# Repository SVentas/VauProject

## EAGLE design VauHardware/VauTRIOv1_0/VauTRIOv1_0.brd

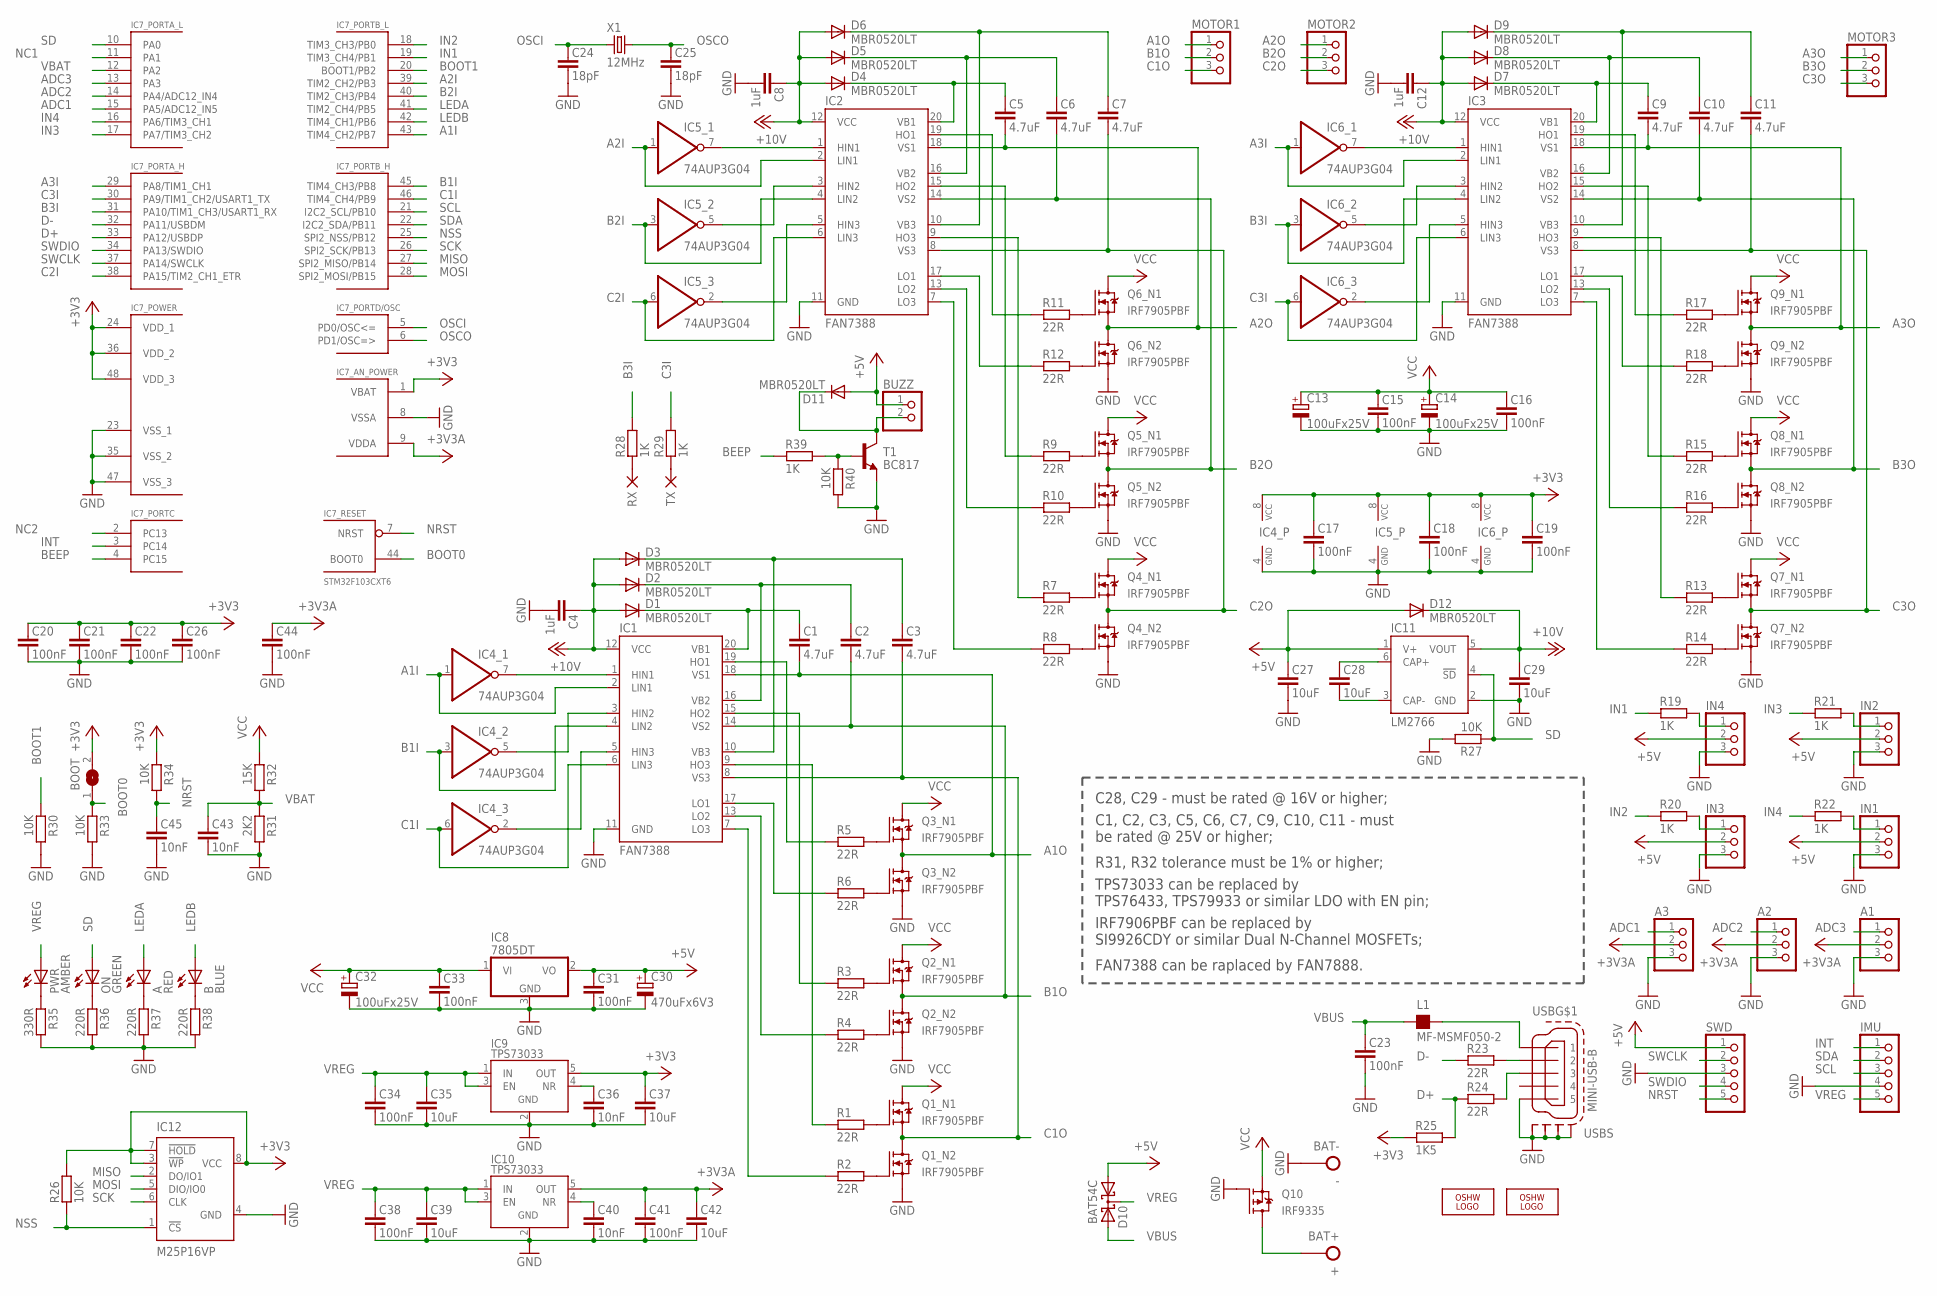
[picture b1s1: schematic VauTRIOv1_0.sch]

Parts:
+: BAT+; PAD20S
-: BAT-; PAD20R
A: RED; CHIPLED_0805
A1, A2, A3: PINHD-1X3; 1X03
B: BLUE; CHIPLED_0805
BOOT: SJ
BUZZ: PINHD-1X2; 1X02
C1, C2, C3, C5, C6, C7, C9, C10, C11: 4.7uF; C0805
C4, C8, C12: 1uF; C0603G
C13, C14: 100uFx25V; E2,5-7
C15, C16, C17, C18, C19, C20, C21, C22, C23, C26, C31, C33, C34, C38, C41, C44: 100nF; C0603G
C24, C25: 18pF; C0603G
C27, C29, C35, C37, C39, C42: 10uF; C0805G
C28: 10uF; C0805
C30: 470uFx6V3; SMC_D
C32: 100uFx25V; SMC_D
C36, C40, C43, C45: 10nF; C0603G
D1, D2, D3, D4, D5, D6, D7, D8, D9, D11, D12: MBR0520LT; SOD123
D10: BAT54C; SOT23
IC1, IC2, IC3: FAN7388; SOIC-20
IC4, IC5, IC6: 74AUP3G04; R-PDSO-G8
IC7: STM32F103CXT6; LQFP48
IC8: 7805DT; TO252
IC9, IC10: TPS73033; SOT23-5
IC11: LM2766; SOT23-6
IC12: M25P16VP; SOIC-8
IMU: PINHD-1X5; 1X05
IN1, IN2, IN3, IN4: PINHD-1X3; 1X03
L1: MF-MSMF050-2; L0603
LOGO1: OSHW_LOGO_10MILX0350-NT; OSHW_10X350_NOTEXT
LOGO2: OSHW_LOGO_FILLX0150-NT; OSHW_FILLX150_NOTEXT
MOTOR1, MOTOR2, MOTOR3: PINHD-1X3MOT; 1X03M
ON: GREEN; CHIPLED_0805
PWR: AMBER; CHIPLED_0805
Q1, Q2, Q3, Q4, Q5, Q6, Q7, Q8, Q9: IRF7905PBF; SOIC-8
Q10: IRF9335; SOIC-8
R1, R2, R3, R4, R5, R6, R7, R8, R9, R10, R11, R12, R13, R14, R15, R16, R17, R18, R23, R24: 22R; R0603
R19, R20, R21, R22, R28, R29, R39: 1K; R0603
R25: 1K5; R0603
R26, R34: 10K; R0603
R27, R30, R33, R40: 10K; R0603G
R31: 2K2; R0603G
R32: 15K; R0603
R35: 330R; R0603G
R36, R37, R38: 220R; R0603G
RX: PAD-SMD10R; SMD10R
SWD: PINHD-1X5; 1X05
T1: BC817; SOT23-BEC
TX: PAD-SMD10R; SMD10R
USB: MINI-USB-B; 32005-201
X1: 12MHz; HC49/S

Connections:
+3V3: BOOT.2, C17.1, C18.1, C19.1, C20.1, C21.1, C22.1, C26.1, C37.1, IC4.8 (VCC), IC5.8 (VCC), IC6.8 (VCC), IC7.1 (VBAT), IC7.24 (VDD_1), IC7.36 (VDD_2), IC7.48 (VDD_3), IC9.5 (OUT), IC12.3 (!WP), IC12.7 (!HOLD), IC12.8 (VCC), R25.1, R26.2, R34.1
+3V3A: A1.2, A2.2, A3.2, C41.1, C42.1, C44.1, IC7.9 (VDDA), IC10.5 (OUT)
+5V: BUZZ.1, C27.1, C30.+, C31.1, D10.1 (A1), D11.A, D12.A, IC8.2 (VO), IC11.1 (V+), IN1.2, IN2.2, IN3.2, IN4.2, SWD.1
+12V: C4.1, C8.1, C12.1, C29.1, D1.A, D2.A, D3.A, D4.A, D5.A, D6.A, D7.A, D8.A, D9.A, D12.C, IC1.12 (VCC), IC2.12 (VCC), IC3.12 (VCC), IC11.5 (VOUT)
A1I: IC1.2 (LIN1), IC4.1 (A), IC7.43 (TIM4_CH2/PB7)
A1O: C1.2, IC1.18 (VS1), MOTOR1.1, Q3.3 (N-S), Q3.7 (N-D), Q3.8 (N-D)
A2I: IC2.2 (LIN1), IC5.1 (A), IC7.39 (TIM2_CH2/PB3)
A2O: C5.2, IC2.18 (VS1), MOTOR2.1, Q6.3 (N-S), Q6.7 (N-D), Q6.8 (N-D)
A3I: IC3.2 (LIN1), IC6.1 (A), IC7.29 (PA8/TIM1_CH1)
A3O: C9.2, IC3.18 (VS1), MOTOR3.1, Q9.3 (N-S), Q9.7 (N-D), Q9.8 (N-D)
ADC1: A3.1, IC7.15 (PA5/ADC12_IN5)
ADC2: A2.1, IC7.14 (PA4/ADC12_IN4)
ADC3: A1.1, IC7.13 (PA3)
B1I: IC1.4 (LIN2), IC4.3 (A), IC7.45 (TIM4_CH3/PB8)
B1O: C2.2, IC1.14 (VS2), MOTOR1.2, Q2.3 (N-S), Q2.7 (N-D), Q2.8 (N-D)
B2I: IC2.4 (LIN2), IC5.3 (A), IC7.40 (TIM2_CH3/PB4)
B2O: C6.2, IC2.14 (VS2), MOTOR2.2, Q5.3 (N-S), Q5.7 (N-D), Q5.8 (N-D)
B3I: IC3.4 (LIN2), IC6.3 (A), IC7.31 (PA10/TIM1_CH3/USART1_RX), R28.2
B3O: C10.2, IC3.14 (VS2), MOTOR3.2, Q8.3 (N-S), Q8.7 (N-D), Q8.8 (N-D)
BAT+: +.P$1, Q10.5 (P-D), Q10.6 (P-D), Q10.7 (P-D), Q10.8 (P-D)
BEEP: IC7.4 (PC15), R39.1
BOOT0: BOOT.1, IC7.44 (BOOT0), R33.1
BOOT1: IC7.20 (BOOT1/PB2), R30.1
C1I: IC1.6 (LIN3), IC4.6 (A), IC7.46 (TIM4_CH4/PB9)
C1O: C3.2, IC1.8 (VS3), MOTOR1.3, Q1.3 (N-S), Q1.7 (N-D), Q1.8 (N-D)
C2I: IC2.6 (LIN3), IC5.6 (A), IC7.38 (PA15/TIM2_CH1_ETR)
C2O: C7.2, IC2.8 (VS3), MOTOR2.3, Q4.3 (N-S), Q4.7 (N-D), Q4.8 (N-D)
C3I: IC3.6 (LIN3), IC6.6 (A), IC7.30 (PA9/TIM1_CH2/USART1_TX), R29.2
C3O: C11.2, IC3.8 (VS3), MOTOR3.3, Q7.3 (N-S), Q7.7 (N-D), Q7.8 (N-D)
D+: IC7.33 (PA12/USBDP), R24.1, R25.2
D-: IC7.32 (PA11/USBDM), R23.1
GND: -.P$1, A1.3, A2.3, A3.3, C4.2, C8.2, C12.2, C13.-, C14.-, C15.2, C16.2, C17.2, C18.2, C19.2, C20.2, C21.2, C22.2, C23.2, C24.2, C25.2, C26.2, C27.2, C29.2, C30.-, C31.2, C32.-, C33.2, C34.2, C35.2, C36.2, C37.2, C38.2, C39.2, C40.2, C41.2, C42.2, C43.2, C44.2, C45.2, IC1.11 (GND), IC2.11 (GND), IC3.11 (GND), IC4.4 (GND), IC5.4 (GND), IC6.4 (GND), IC7.8 (VSSA), IC7.23 (VSS_1), IC7.35 (VSS_2), IC7.47 (VSS_3), IC8.3 (GND), IC9.2 (GND), IC10.2 (GND), IC11.2 (GND), IC12.4 (GND), IMU.4, IN1.3, IN2.3, IN3.3, IN4.3, Q1.1 (N-S), Q2.1 (N-S), Q3.1 (N-S), Q4.1 (N-S), Q5.1 (N-S), Q6.1 (N-S), Q7.1 (N-S), Q8.1 (N-S), Q9.1 (N-S), Q10.4 (P-G), R27.2, R30.2, R31.2, R33.2, R35.2, R36.2, R37.2, R38.2, R40.2, SWD.3, T1.E, USB.5, USB.M1 (S1), USB.M2 (S2), USB.M3 (S3), USB.M4 (S4)
IN1: IC7.19 (TIM3_CH4/PB1), R19.1
IN2: IC7.18 (TIM3_CH3/PB0), R20.1
IN3: IC7.17 (PA7/TIM3_CH2), R21.1
IN4: IC7.16 (PA6/TIM3_CH1), R22.1
INT: IC7.3 (PC14), IMU.1
LEDA: A.A, IC7.41 (TIM2_CH4/PB5)
LEDB: B.A, IC7.42 (TIM4_CH1/PB6)
MISO: IC7.27 (SPI2_MISO/PB14), IC12.2 (DO/IO1)
MOSI: IC7.28 (SPI2_MOSI/PB15), IC12.5 (DIO/IO0)
unnamed: IC1.19 (HO1), R5.1
unnamed: Q5.4 (N-G), R9.2
unnamed: Q5.2 (N-G), R10.2
unnamed: Q2.4 (N-G), R3.2
unnamed: Q2.2 (N-G), R4.2
unnamed: Q3.4 (N-G), R5.2
unnamed: Q3.2 (N-G), R6.2
unnamed: IC1.3 (HIN2), IC4.5 (Y)
unnamed: C1.1, D1.C, IC1.20 (VB1)
unnamed: C2.1, D2.C, IC1.16 (VB2)
unnamed: C3.1, D3.C, IC1.10 (VB3)
unnamed: Q6.4 (N-G), R11.2
unnamed: Q6.2 (N-G), R12.2
unnamed: IN4.1, R19.2
unnamed: Q1.4 (N-G), R1.2
unnamed: Q1.2 (N-G), R2.2
unnamed: IC1.1 (HIN1), IC4.7 (Y)
unnamed: PWR.C, R35.1
unnamed: IC1.5 (HIN3), IC4.2 (Y)
unnamed: ON.C, R36.1
unnamed: R23.2, USB.2
unnamed: A.C, R37.1
unnamed: C5.1, D4.C, IC2.20 (VB1)
unnamed: C6.1, D5.C, IC2.16 (VB2)
unnamed: IC1.17 (LO1), R6.1
unnamed: IC1.15 (HO2), R3.1
unnamed: IC1.13 (LO2), R4.1
unnamed: IC1.7 (LO3), R2.1
unnamed: IC1.9 (HO3), R1.1
unnamed: C7.1, D6.C, IC2.10 (VB3)
unnamed: Q4.4 (N-G), R7.2
unnamed: Q4.2 (N-G), R8.2
unnamed: IC2.1 (HIN1), IC5.7 (Y)
unnamed: IN3.1, R20.2
unnamed: IC2.3 (HIN2), IC5.5 (Y)
unnamed: R24.2, USB.3
unnamed: IC2.5 (HIN3), IC5.2 (Y)
unnamed: IN2.1, R21.2
unnamed: IC2.17 (LO1), R12.1
unnamed: IC2.15 (HO2), R9.1
unnamed: IC2.13 (LO2), R10.1
unnamed: IC2.7 (LO3), R8.1
unnamed: IC2.9 (HO3), R7.1
unnamed: IC2.19 (HO1), R11.1
unnamed: Q8.4 (N-G), R15.2
unnamed: Q8.2 (N-G), R16.2
unnamed: Q9.4 (N-G), R17.2
unnamed: Q9.2 (N-G), R18.2
unnamed: IN1.1, R22.2
unnamed: C9.1, D7.C, IC3.20 (VB1)
unnamed: C10.1, D8.C, IC3.16 (VB2)
unnamed: C11.1, D9.C, IC3.10 (VB3)
unnamed: Q7.4 (N-G), R13.2
unnamed: Q7.2 (N-G), R14.2
unnamed: IC3.1 (HIN1), IC6.7 (Y)
unnamed: L1.2, USB.1
unnamed: IC3.3 (HIN2), IC6.5 (Y)
unnamed: B.C, R38.1
unnamed: IC3.5 (HIN3), IC6.2 (Y)
unnamed: BUZZ.2, D11.C, T1.C
unnamed: IC3.17 (LO1), R18.1
unnamed: IC3.15 (HO2), R15.1
unnamed: IC3.13 (LO2), R16.1
unnamed: IC3.7 (LO3), R14.1
unnamed: IC3.9 (HO3), R13.1
unnamed: IC3.19 (HO1), R17.1
unnamed: C28.1, IC11.6 (CAP+)
unnamed: C28.2, IC11.3 (CAP-)
unnamed: R28.1, RX.PAD
unnamed: R29.1, TX.PAD
unnamed: R39.2, R40.1, T1.B
unnamed: C40.1, IC10.4 (NR)
unnamed: C36.1, IC9.4 (NR)
NC1: IC7.11 (PA1)
NC2: IC7.2 (PC13)
NRST: C45.1, IC7.7 (NRST), R34.2, SWD.5
NSS: IC7.25 (SPI2_NSS/PB12), IC12.1 (!CS), R26.1
OSCI: C24.1, IC7.5 (PD0/OSC<=), X1.1
OSCO: C25.1, IC7.6 (PD1/OSC=>), X1.2
SCK: IC7.26 (SPI2_SCK/PB13), IC12.6 (CLK)
SCL: IC7.21 (I2C2_SCL/PB10), IMU.3
SD: IC7.10 (PA0), IC11.4 (!SD), ON.A, R27.1
SDA: IC7.22 (I2C2_SDA/PB11), IMU.2
SWCLK: IC7.37 (PA14/SWCLK), SWD.2
SWDIO: IC7.34 (PA13/SWDIO), SWD.4
VBAT: C43.1, IC7.12 (PA2), R31.1, R32.2
VBUS: C23.1, D10.2 (A2), L1.1
VCC: C13.+, C14.+, C15.1, C16.1, C32.+, C33.1, IC8.1 (VI), Q1.5 (N-D), Q1.6 (N-D), Q2.5 (N-D), Q2.6 (N-D), Q3.5 (N-D), Q3.6 (N-D), Q4.5 (N-D), Q4.6 (N-D), Q5.5 (N-D), Q5.6 (N-D), Q6.5 (N-D), Q6.6 (N-D), Q7.5 (N-D), Q7.6 (N-D), Q8.5 (N-D), Q8.6 (N-D), Q9.5 (N-D), Q9.6 (N-D), Q10.1 (P-S), Q10.2 (P-S), Q10.3 (P-S), R32.1
VREG: C34.1, C35.1, C38.1, C39.1, D10.3 (CC), IC9.1 (IN), IC9.3 (EN), IC10.1 (IN), IC10.3 (EN), IMU.5, PWR.A

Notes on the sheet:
C1, C2, C3, C5, C6, C7, C9, C10, C11 - must be rated @ 25V or higher;
C28, C29 - must be rated @ 16V or higher;
TPS73033 can be replaced by TPS76433, TPS79933 or similar LDO with EN pin;
IRF7906PBF can be replaced by SI9926CDY or similar Dual N-Channel MOSFETs;
R31, R32 tolerance must be 1% or higher;
FAN7388 can be raplaced by FAN7888.

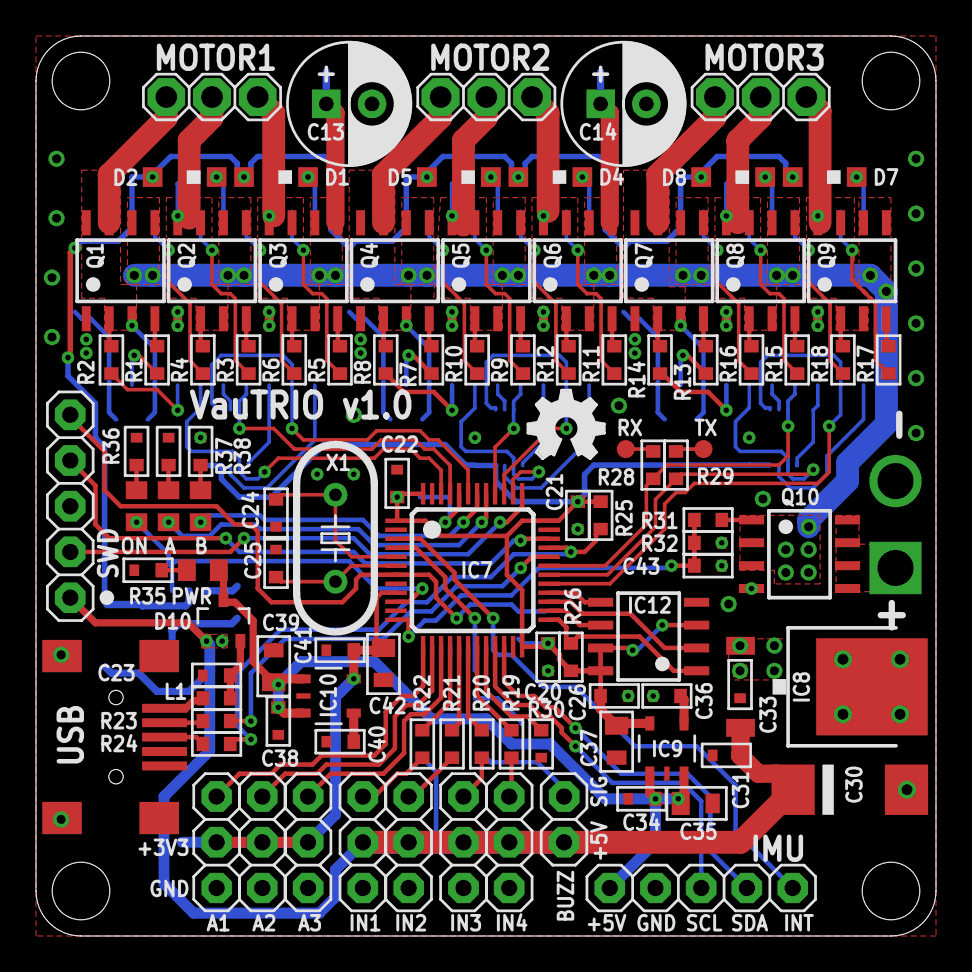
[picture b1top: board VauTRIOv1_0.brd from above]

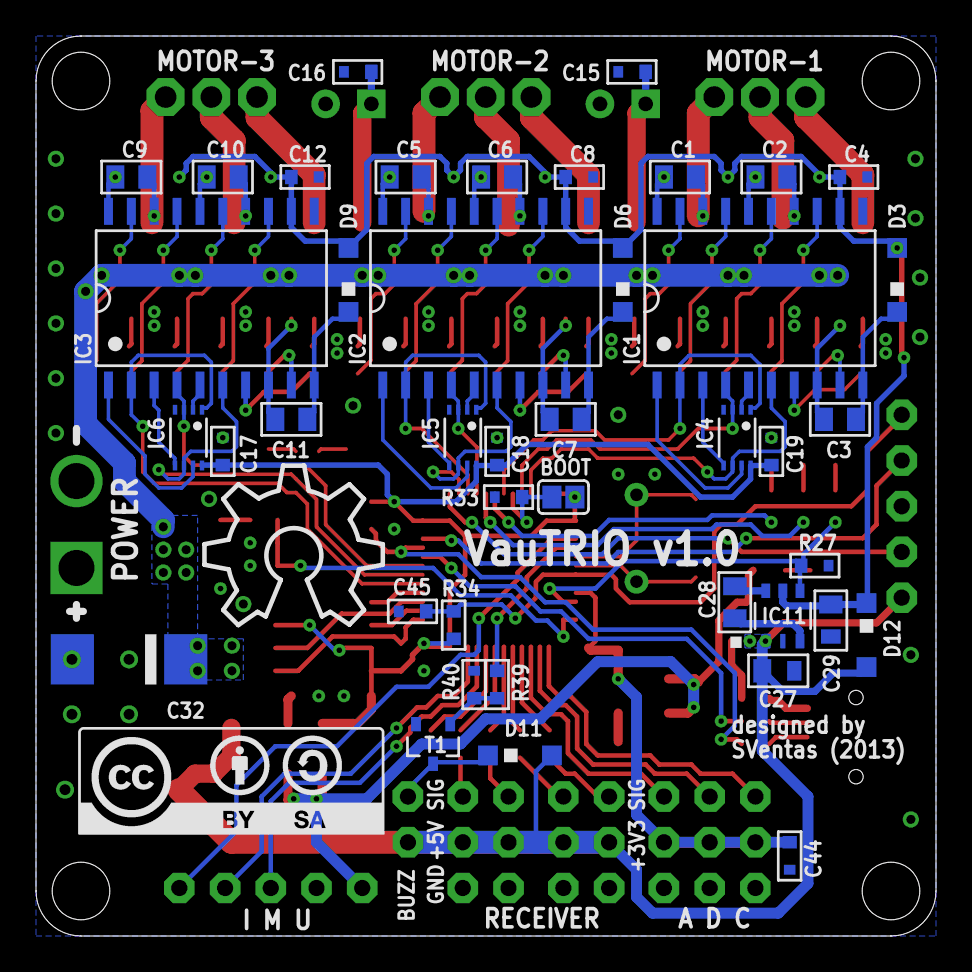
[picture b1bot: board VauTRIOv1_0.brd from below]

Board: 2 copper layers, 50.0 x 50.0 mm, 147 parts (43 on the bottom side), 128 nets.

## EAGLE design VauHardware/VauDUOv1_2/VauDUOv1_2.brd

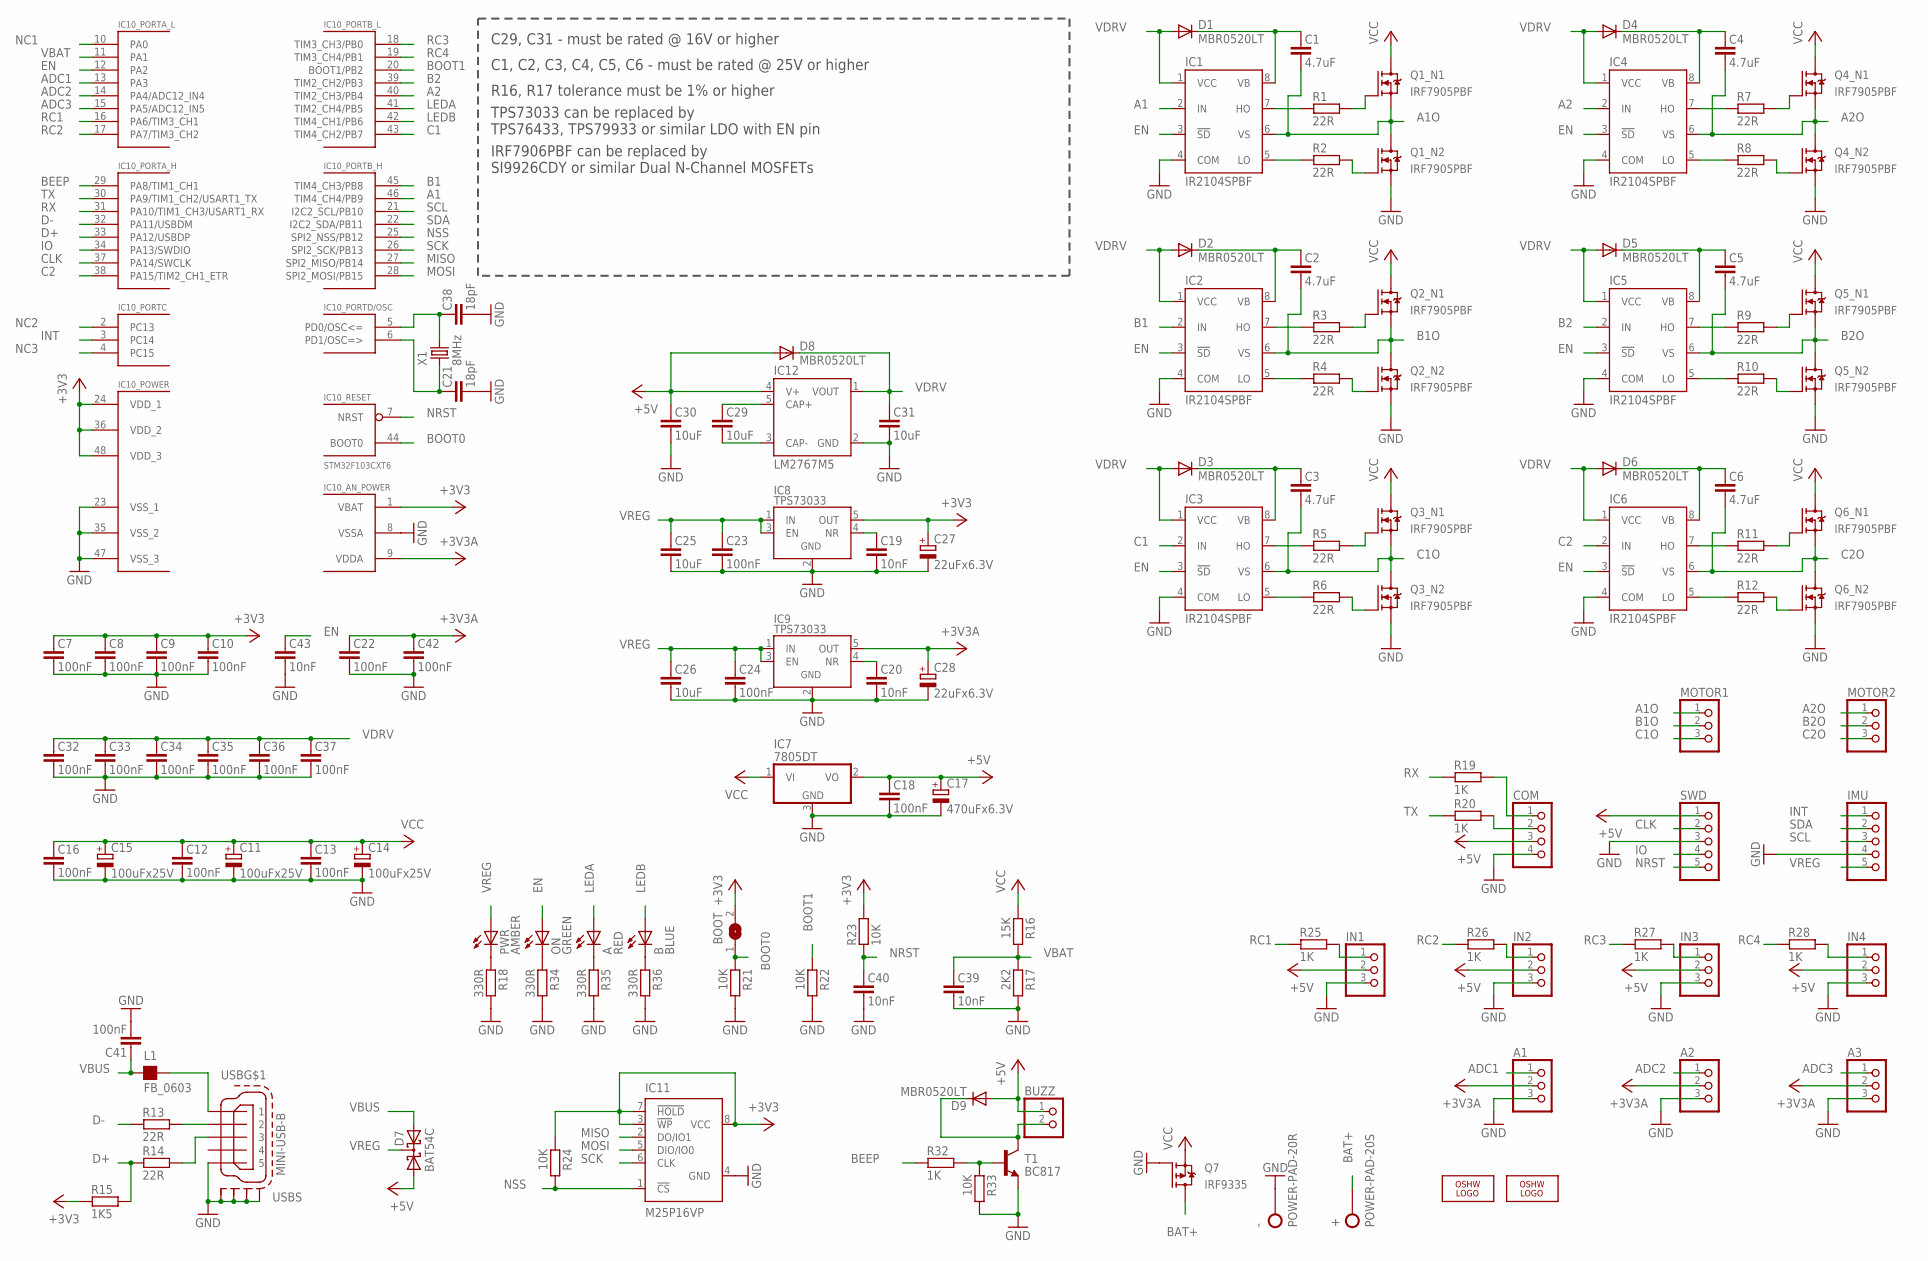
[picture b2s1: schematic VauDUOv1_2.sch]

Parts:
+: POWER-PAD-20S; PAD20S
-: POWER-PAD-20R; PAD20R
A: RED; CHIPLED_0805
A1, A2, A3: PINHD-1X3; 1X03
B: BLUE; CHIPLED_0805
BOOT: SJ
BUZZ: PINHD-1X2; 1X02
C1, C2, C3, C4, C5, C6: 4.7uF; C0805
C7, C8, C9, C10, C12, C13, C16, C18, C22, C23, C24, C32, C33, C34, C35, C36, C37, C41, C42: 100nF; C0603G
C11, C14: 100uFx25V; E2,5-7
C15: 100uFx25V; SMC_D
C17: 470uFx6.3V; SMC_D
C19, C20, C39, C40, C43: 10nF; C0603G
C21, C38: 18pF; C0603G
C25, C26, C30, C31: 10uF; C0805G
C27, C28: 22uFx6.3V; SMC_A
C29: 10uF; C0805
COM: PINHD-1X4; 1X04
D1, D2, D3, D4, D5, D6, D8, D9: MBR0520LT; SOD123
D7: BAT54C; SOT23
IC1, IC2, IC3, IC4, IC5, IC6: IR2104SPBF; SOIC-8
IC7: 7805DT; TO252
IC8, IC9: TPS73033; SOT23-5
IC10: STM32F103CXT6; LQFP48
IC11: M25P16VP; SOIC-8
IC12: LM2767M5; SOT23-5
IMU: PINHD-1X5; 1X05
IN1, IN2, IN3, IN4: PINHD-1X3; 1X03
L1: FB_0603; L0603
LOGO1: OSHW_LOGO_10MILX0350-NT; OSHW_10X350_NOTEXT
LOGO2: OSHW_LOGO_FILLX0150-NT; OSHW_FILLX150_NOTEXT
MOTOR1, MOTOR2: PINHD-1X3MOT; 1X03M
ON: GREEN; CHIPLED_0805
PWR: AMBER; CHIPLED_0805
Q1, Q2, Q3, Q4, Q5, Q6: IRF7905PBF; SOIC-8
Q7: IRF9335; SOIC-8
R1, R2, R3, R4, R5, R6, R7, R8, R9, R10, R11, R12, R13, R14: 22R; R0603
R15: 1K5; R0603
R16: 15K; R0603
R17: 2K2; R0603G
R18, R34, R35, R36: 330R; R0603G
R19, R20, R25, R26, R27, R28, R32: 1K; R0603
R21, R22, R33: 10K; R0603G
R23, R24: 10K; R0603
SWD: PINHD-1X5; 1X05
T1: BC817; SOT23-BEC
USB: MINI-USB-B; 32005-201
X1: 8MHz; HC49/S

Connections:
+3V3: BOOT.2, C7.1, C8.1, C9.1, C10.1, C27.+, IC8.5 (OUT), IC10.1 (VBAT), IC10.24 (VDD_1), IC10.36 (VDD_2), IC10.48 (VDD_3), IC11.3 (!WP), IC11.7 (!HOLD), IC11.8 (VCC), R15.1, R23.2, R24.1
+3V3A: A1.2, A2.2, A3.2, C22.1, C28.+, C42.1, IC9.5 (OUT), IC10.9 (VDDA)
+5V: BUZZ.1, C17.+, C18.1, C30.1, COM.3, D7.1 (A1), D8.A, D9.A, IC7.2 (VO), IC12.4 (V+), IN1.2, IN2.2, IN3.2, IN4.2, SWD.1
A1: IC1.2 (IN), IC10.46 (TIM4_CH4/PB9)
A1O: C1.2, IC1.6 (VS), MOTOR1.1, Q1.3 (N-S), Q1.7 (N-D), Q1.8 (N-D)
A2: IC4.2 (IN), IC10.40 (TIM2_CH3/PB4)
A2O: C4.2, IC4.6 (VS), MOTOR2.1, Q4.3 (N-S), Q4.7 (N-D), Q4.8 (N-D)
ADC1: A1.1, IC10.13 (PA3)
ADC2: A2.1, IC10.14 (PA4/ADC12_IN4)
ADC3: A3.1, IC10.15 (PA5/ADC12_IN5)
B1: IC2.2 (IN), IC10.45 (TIM4_CH3/PB8)
B1O: C2.2, IC2.6 (VS), MOTOR1.2, Q2.3 (N-S), Q2.7 (N-D), Q2.8 (N-D)
B2: IC5.2 (IN), IC10.39 (TIM2_CH2/PB3)
B2O: C5.2, IC5.6 (VS), MOTOR2.2, Q5.3 (N-S), Q5.7 (N-D), Q5.8 (N-D)
BAT+: +.P$1, Q7.5 (P-D), Q7.6 (P-D), Q7.7 (P-D), Q7.8 (P-D)
BEEP: IC10.29 (PA8/TIM1_CH1), R32.1
BOOT0: BOOT.1, IC10.44 (BOOT0), R21.1
BOOT1: IC10.20 (BOOT1/PB2), R22.1
C1: IC3.2 (IN), IC10.43 (TIM4_CH2/PB7)
C1O: C3.2, IC3.6 (VS), MOTOR1.3, Q3.3 (N-S), Q3.7 (N-D), Q3.8 (N-D)
C2: IC6.2 (IN), IC10.38 (PA15/TIM2_CH1_ETR)
C2O: C6.2, IC6.6 (VS), MOTOR2.3, Q6.3 (N-S), Q6.7 (N-D), Q6.8 (N-D)
CLK: IC10.37 (PA14/SWCLK), SWD.2
D+: IC10.33 (PA12/USBDP), R14.1, R15.2
D-: IC10.32 (PA11/USBDM), R13.1
EN: C43.1, IC1.3 (!SD), IC2.3 (!SD), IC3.3 (!SD), IC4.3 (!SD), IC5.3 (!SD), IC6.3 (!SD), IC10.12 (PA2), ON.A
GND: -.P$1, A1.3, A2.3, A3.3, C7.2, C8.2, C9.2, C10.2, C11.-, C12.2, C13.2, C14.-, C15.-, C16.2, C17.-, C18.2, C19.2, C20.2, C21.2, C22.2, C23.2, C24.2, C25.2, C26.2, C27.-, C28.-, C30.2, C31.2, C32.2, C33.2, C34.2, C35.2, C36.2, C37.2, C38.2, C39.2, C40.2, C41.2, C42.2, C43.2, COM.4, IC1.4 (COM), IC2.4 (COM), IC3.4 (COM), IC4.4 (COM), IC5.4 (COM), IC6.4 (COM), IC7.3 (GND), IC8.2 (GND), IC9.2 (GND), IC10.8 (VSSA), IC10.23 (VSS_1), IC10.35 (VSS_2), IC10.47 (VSS_3), IC11.4 (GND), IC12.2 (GND), IMU.4, IN1.3, IN2.3, IN3.3, IN4.3, Q1.1 (N-S), Q2.1 (N-S), Q3.1 (N-S), Q4.1 (N-S), Q5.1 (N-S), Q6.1 (N-S), Q7.4 (P-G), R17.2, R18.2, R21.2, R22.2, R33.2, R34.2, R35.2, R36.2, SWD.3, T1.E, USB.5, USB.M1 (S1), USB.M2 (S2), USB.M3 (S3), USB.M4 (S4)
INT: IC10.3 (PC14), IMU.1
IO: IC10.34 (PA13/SWDIO), SWD.4
LEDA: A.A, IC10.41 (TIM2_CH4/PB5)
LEDB: B.A, IC10.42 (TIM4_CH1/PB6)
MISO: IC10.27 (SPI2_MISO/PB14), IC11.2 (DO/IO1)
MOSI: IC10.28 (SPI2_MOSI/PB15), IC11.5 (DIO/IO0)
unnamed: IC2.7 (HO), R3.1
unnamed: Q1.2 (N-G), R2.2
unnamed: Q1.4 (N-G), R1.2
unnamed: IC2.5 (LO), R4.1
unnamed: C2.1, D2.C, IC2.8 (VB)
unnamed: C1.1, D1.C, IC1.8 (VB)
unnamed: Q2.2 (N-G), R4.2
unnamed: Q2.4 (N-G), R3.2
unnamed: IC3.7 (HO), R5.1
unnamed: IC3.5 (LO), R6.1
unnamed: C3.1, D3.C, IC3.8 (VB)
unnamed: Q3.2 (N-G), R6.2
unnamed: Q3.4 (N-G), R5.2
unnamed: IC4.7 (HO), R7.1
unnamed: IC4.5 (LO), R8.1
unnamed: C4.1, D4.C, IC4.8 (VB)
unnamed: Q4.2 (N-G), R8.2
unnamed: Q4.4 (N-G), R7.2
unnamed: IC1.7 (HO), R1.1
unnamed: IC1.5 (LO), R2.1
unnamed: IC5.7 (HO), R9.1
unnamed: IC5.5 (LO), R10.1
unnamed: C5.1, D5.C, IC5.8 (VB)
unnamed: Q5.2 (N-G), R10.2
unnamed: Q5.4 (N-G), R9.2
unnamed: IC6.7 (HO), R11.1
unnamed: IC6.5 (LO), R12.1
unnamed: C6.1, D6.C, IC6.8 (VB)
unnamed: Q6.2 (N-G), R12.2
unnamed: Q6.4 (N-G), R11.2
unnamed: R13.2, USB.2
unnamed: C29.1, IC12.5 (CAP+)
unnamed: R14.2, USB.3
unnamed: C19.1, IC8.4 (NR)
unnamed: IN1.1, R25.2
unnamed: C20.1, IC9.4 (NR)
unnamed: L1.2, USB.1
unnamed: C21.1, IC10.6 (PD1/OSC=>), X1.1
unnamed: C38.1, IC10.5 (PD0/OSC<=), X1.2
unnamed: C29.2, IC12.3 (CAP-)
unnamed: PWR.C, R18.1
unnamed: COM.1, R19.2
unnamed: COM.2, R20.2
unnamed: IN2.1, R26.2
unnamed: IN3.1, R27.2
unnamed: IN4.1, R28.2
unnamed: BUZZ.2, D9.C, T1.C
unnamed: R32.2, R33.1, T1.B
unnamed: ON.C, R34.1
unnamed: A.C, R35.1
unnamed: B.C, R36.1
NC1: IC10.10 (PA0)
NC2: IC10.2 (PC13)
NC3: IC10.4 (PC15)
NRST: C40.1, IC10.7 (NRST), R23.1, SWD.5
NSS: IC10.25 (SPI2_NSS/PB12), IC11.1 (!CS), R24.2
RC1: IC10.16 (PA6/TIM3_CH1), R25.1
RC2: IC10.17 (PA7/TIM3_CH2), R26.1
RC3: IC10.18 (TIM3_CH3/PB0), R27.1
RC4: IC10.19 (TIM3_CH4/PB1), R28.1
RX: IC10.31 (PA10/TIM1_CH3/USART1_RX), R19.1
SCK: IC10.26 (SPI2_SCK/PB13), IC11.6 (CLK)
SCL: IC10.21 (I2C2_SCL/PB10), IMU.3
SDA: IC10.22 (I2C2_SDA/PB11), IMU.2
TX: IC10.30 (PA9/TIM1_CH2/USART1_TX), R20.1
VBAT: C39.1, IC10.11 (PA1), R16.2, R17.1
VBUS: C41.1, D7.2 (A2), L1.1
VCC: C11.+, C12.1, C13.1, C14.+, C15.+, C16.1, IC7.1 (VI), Q1.5 (N-D), Q1.6 (N-D), Q2.5 (N-D), Q2.6 (N-D), Q3.5 (N-D), Q3.6 (N-D), Q4.5 (N-D), Q4.6 (N-D), Q5.5 (N-D), Q5.6 (N-D), Q6.5 (N-D), Q6.6 (N-D), Q7.1 (P-S), Q7.2 (P-S), Q7.3 (P-S), R16.1
VDRV: C31.1, C32.1, C33.1, C34.1, C35.1, C36.1, C37.1, D1.A, D2.A, D3.A, D4.A, D5.A, D6.A, D8.C, IC1.1 (VCC), IC2.1 (VCC), IC3.1 (VCC), IC4.1 (VCC), IC5.1 (VCC), IC6.1 (VCC), IC12.1 (VOUT)
VREG: C23.1, C24.1, C25.1, C26.1, D7.3 (CC), IC8.1 (IN), IC8.3 (EN), IC9.1 (IN), IC9.3 (EN), IMU.5, PWR.A

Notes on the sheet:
C1, C2, C3, C4, C5, C6 - must be rated @ 25V or higher
C29, C31 - must be rated @ 16V or higher
TPS73033 can be replaced by TPS76433, TPS79933 or similar LDO with EN pin
IRF7906PBF can be replaced by SI9926CDY or similar Dual N-Channel MOSFETs
R16, R17 tolerance must be 1% or higher

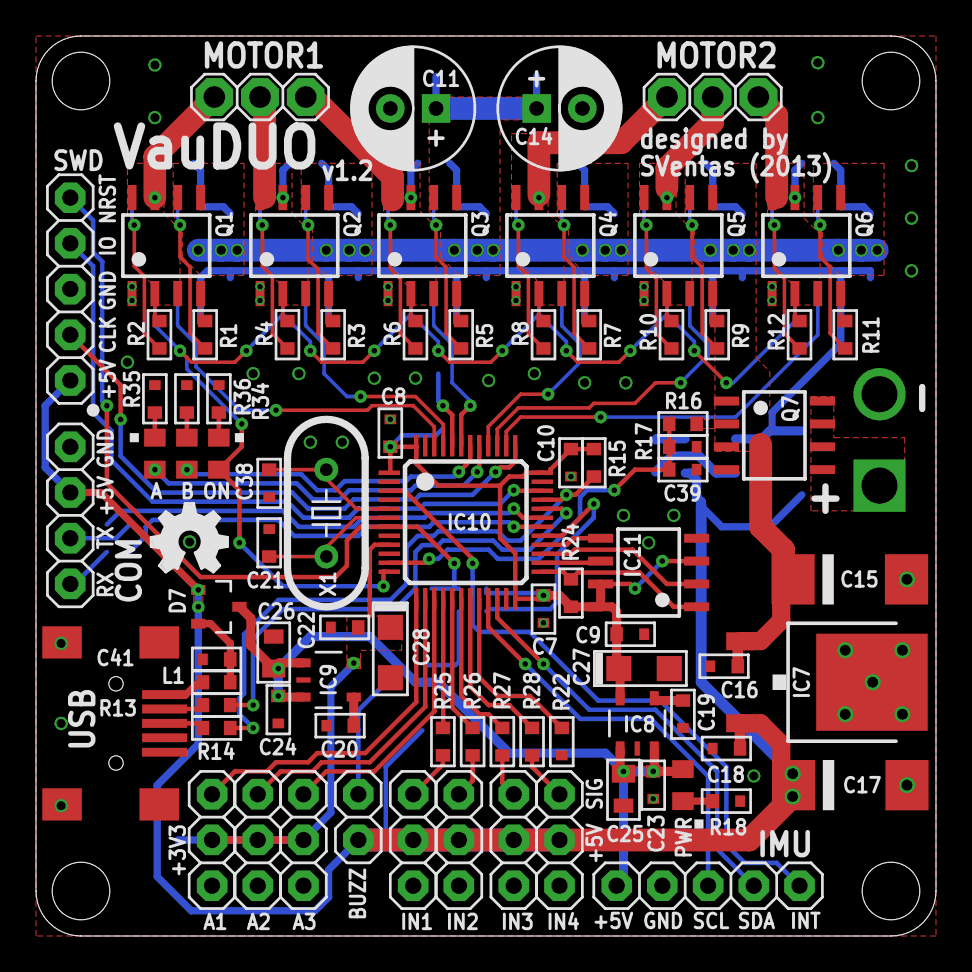
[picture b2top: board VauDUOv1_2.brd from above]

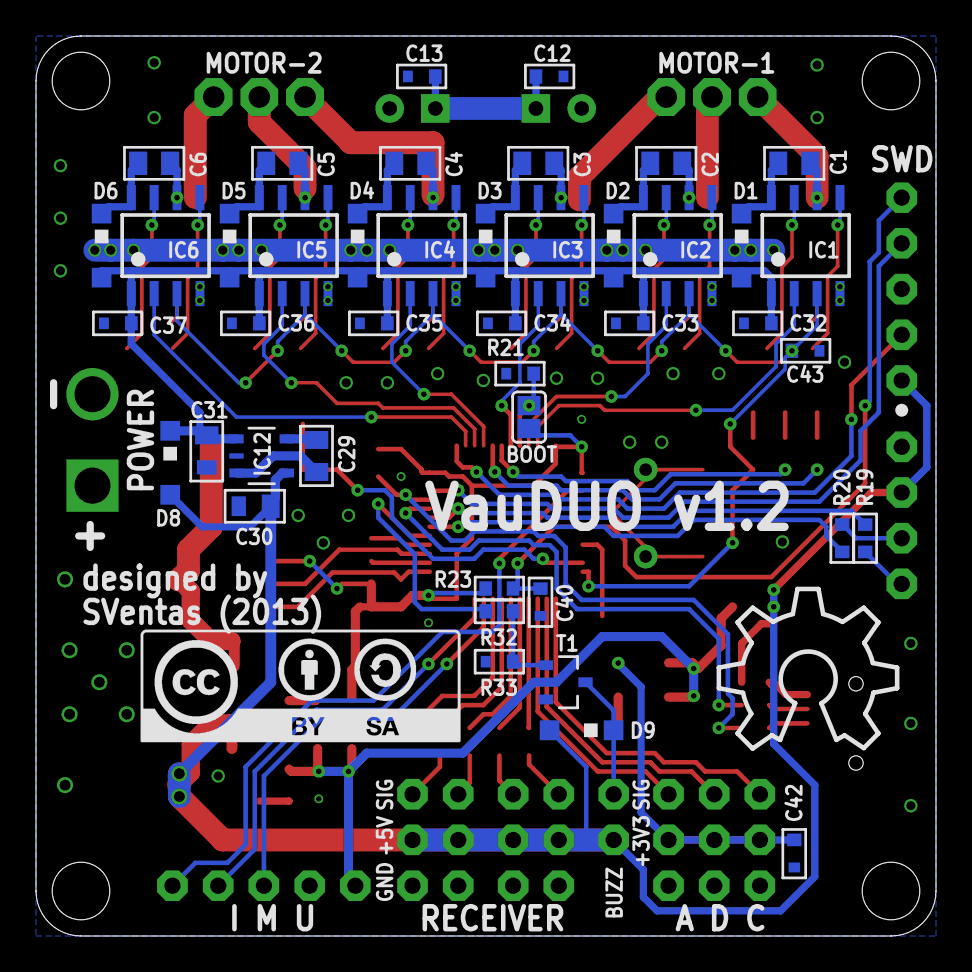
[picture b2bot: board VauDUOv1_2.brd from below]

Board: 2 copper layers, 50.0 x 50.0 mm, 130 parts (44 on the bottom side), 100 nets.

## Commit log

2013-12-11 VauDUOv1_2 added
2013-12-23 VauTRIOv1_0 added
2013-12-23 minor error fix
2014-01-16 minor cleaning

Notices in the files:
parts and their libraries:
dpads: Copyright (C) 2004, Bob Starr (bobstarr@mindspring.com)
